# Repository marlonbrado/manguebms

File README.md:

# MangueBMS
A bms with charger for 3 to 5 series lithium batteries.
Based on BQ77915 protection circuit and BQ24650 charger.

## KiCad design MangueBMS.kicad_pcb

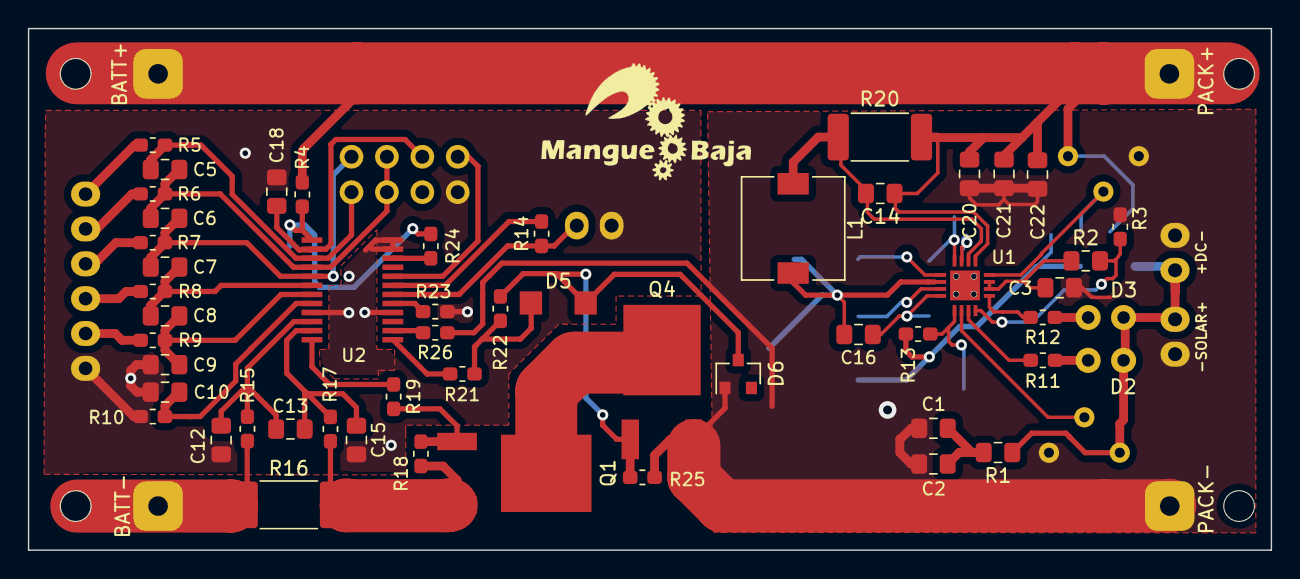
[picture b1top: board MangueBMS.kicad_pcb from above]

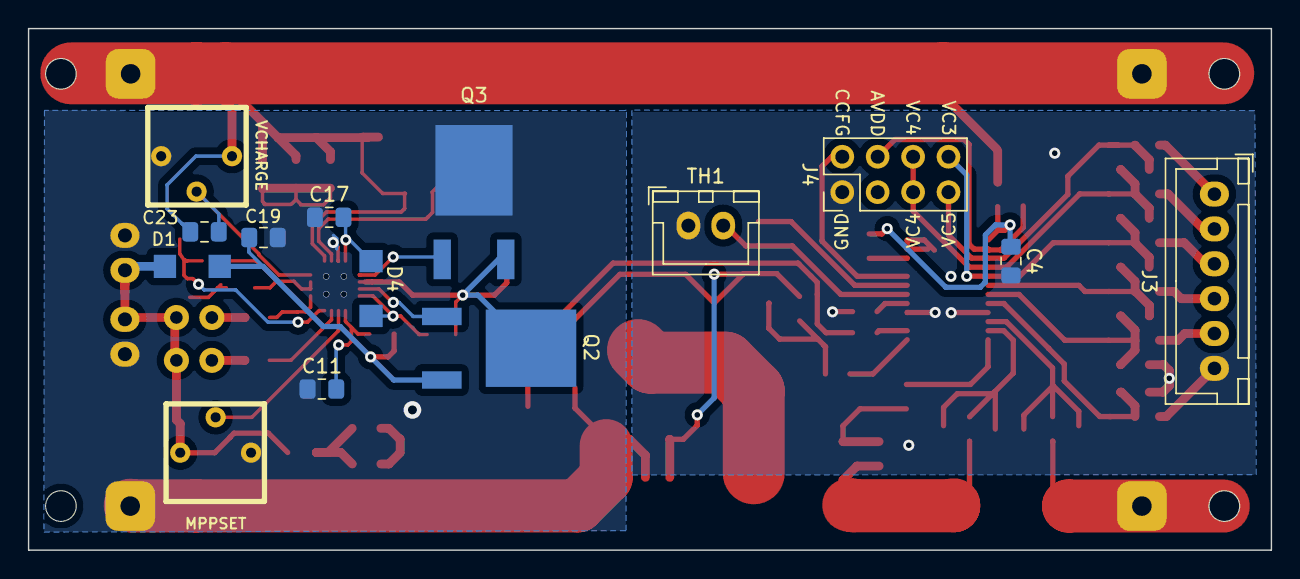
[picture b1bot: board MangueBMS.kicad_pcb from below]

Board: 2 copper layers, 89.2 x 37.4 mm, 73 parts (14 on the bottom side), 50 nets.

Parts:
+DC-: DC IN; DC_IN_PADS
-SOLAR+: SOLAR IN; SOLAR_PANEL_PADS
BATT+: PACK+; PACK_PADS
BATT-: BATT-; PACK_PADS
C1, C2, C3, C11, C17, C22: 1uF 50V; C_0805_2012Metric_Pad1.15x1.40mm_HandSolder
C4, C18: 1uF; C_0805_2012Metric_Pad1.15x1.40mm_HandSolder
C5, C6, C7, C8, C9, C10, C12, C13, C15: 100nF; C_0805_2012Metric_Pad1.15x1.40mm_HandSolder
C14, C16: 100nF 50V; C_0805_2012Metric_Pad1.15x1.40mm_HandSolder
C19, C20, C21: 10uF 50V; C_0805_2012Metric_Pad1.15x1.40mm_HandSolder
C23: 18pF 50V; C_0805_2012Metric_Pad1.15x1.40mm_HandSolder
D1, D4, D5: D_Schottky; DO-241AC
D2, D3: LED; LED_D3.0mm_Clear
D6: 10V Zener; D_SOT-23_ANK
J3: BATTERY INPUT; JST_XH_1x06
J4: Pin Header; PinHeader_2x04_P2.54mm_Vertical
L1: 10uH; L_7.3x7.3_H3.5
MPPSET: 100K Trimpot; BOURNS-3362P_pot
PACK+: PACK+; PACK_PADS
PACK-: PACK-; PACK_PADS
Q1, Q4: Power NMOS; FDD8847L
Q2, Q3: Q_NMOS_GSD; FDD8847L
R1: 2; R_0805_2012Metric_Pad1.15x1.40mm_HandSolder
R2: 10K; R_0805_2012Metric_Pad1.15x1.40mm_HandSolder
R3, R11, R12, R14, R19, R21, R24: 10K; R_0603_1608Metric_Pad1.05x0.95mm_HandSolder
R4, R5, R6, R7, R8, R9, R10: 1K; R_0603_1608Metric_Pad1.05x0.95mm_HandSolder
R13: 10; R_0603_1608Metric_Pad1.05x0.95mm_HandSolder
R15, R17: 100; R_0603_1608Metric_Pad1.05x0.95mm_HandSolder
R16: 10m 2W; R_2512_6332Metric_Pad1.52x3.35mm_HandSolder
R18, R22: 1M; R_0603_1608Metric_Pad1.05x0.95mm_HandSolder
R20: 30m; R_2512_6332Metric_Pad1.52x3.35mm_HandSolder
R23: 750K; R_0603_1608Metric_Pad1.05x0.95mm_HandSolder
R25: 3.3M; R_0603_1608Metric_Pad1.05x0.95mm_HandSolder
R26: 470K; R_0603_1608Metric_Pad1.05x0.95mm_HandSolder
TH1: Thermistor 10K; JST_XH_B2B-XH-A_1x02_P2.50mm_Vertical
U1: BQ24650; BQ24650RVA-VQFN16
U2: BQ7791500; BQ7791500-TSSOP24
VCHARGE: 100K Trimpot; BOURNS-3362P_pot

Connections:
/AVDD: C18.2, J4.4, U2.2
/BTST: C16.1, D4.1, U1.16
/CCFG: J4.2, U2.20
/HIDRV: Q2.1, U1.15
/LODRV: Q3.1, U1.13
/PACK+: BATT+.1, C14.1, C20.1, C21.1, C22.1, C23.1, PACK+.1, R4.1, R20.1, U1.9, VCHARGE.1
/PH: C16.2, L1.2, Q2.2, Q3.3, U1.14
/REGN: C17.2, D4.2, U1.12
/TSC: R2.2, R3.1, U1.4
/VC0: C10.2, R10.2, U2.8
/VC1: C8.2, C9.1, R9.2, U2.7
/VC2: C7.2, C8.1, R8.2, U2.6
/VC3: C6.2, C7.1, J4.8, R7.2, U2.5
/VC4: C5.2, C6.1, J4.5, J4.6, R6.2, U2.4
/VC5: C5.1, J4.7, R5.2, U2.3
/VDD: C4.1, R4.2, R24.2, U2.1
/VIN: +DC-.1, -SOLAR+.1, D1.2, D2.2, D3.2, MPPSET.1, R1.1
GND: C4.2, C9.2, C10.1, C12.1, C15.2, C18.1, J3.6, J4.1, R10.1, R23.1, TH1.1, U2.9, U2.16, U2.23, U2.24
GNDPWR: +DC-.2, -SOLAR+.2, C1.2, C2.2, C3.2, C11.1, C17.1, C19.1, C20.2, C21.2, C22.2, D6.2, MPPSET.3, PACK-.1, Q3.2, Q4.3, R3.2, R25.2, R26.2, U1.11, U1.THERMAL PAD, VCHARGE.3
unnamed: C1.1, C2.1, R1.2
unnamed: C3.1, R2.1, U1.6, U1.7
unnamed: C11.2, R13.2, U1.1
unnamed: C12.2, C13.1, R15.1, U2.10
unnamed: C13.2, C15.1, R17.1, U2.11
unnamed: C14.2, L1.1, R20.2, U1.10
unnamed: C19.2, D1.1, Q2.3, R13.1
unnamed: C23.2, U1.8, VCHARGE.2
unnamed: D2.1, R11.2
unnamed: D3.1, R12.1
unnamed: D5.1, D6.1, Q4.1, R22.2, R25.1
unnamed: D5.2, R21.2, R22.1
unnamed: J3.1, R5.1
unnamed: J3.2, R6.1
unnamed: J3.3, R7.1
unnamed: J3.4, R8.1
unnamed: J3.5, R9.1
unnamed: Q1.1, R18.1, R19.2
unnamed: Q1.2, Q4.2
unnamed: Q1.3, R16.2, R17.2, R18.2
unnamed: R11.1, U1.3
unnamed: R12.2, U1.5
unnamed: BATT-.1, R15.2, R16.1
unnamed: R19.1, U2.12
unnamed: R21.1, U2.13
unnamed: R23.2, U2.17
unnamed: R24.1, U2.22
unnamed: R26.1, U2.14
unnamed: MPPSET.2, U1.2
TS: R14.1, TH1.2, U2.18
VTB: R14.2, U2.19
